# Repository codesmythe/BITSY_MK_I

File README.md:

This board is designed to run the [EmuTOS](https://emutos.sourceforge.io) operating system. EmuTOS is an open-source variant of the Atari ST TOS operating system.

BITSY Mark I is part of system containing this board, a [XOSERA_RCBUS](https://github.com/codesmythe/XOSERA_RCBUS) board for VGA output, a [KEMOJO](https://github.com/codesmythe/KEMOJO) board for
PS/2 keyboard and mouse input, and an RCBus backplane board such as an [SC147](https://smallcomputercentral.com/rcbus/sc100-series/sc147-modular-backplane-rc2014/). Together, this system can run full GUI EmuTOS with 640x240 graphics in 16 colors.

This SBC can also be used by itself, in EmuTOS command-line mode, using the on-board UART for serial input and output at 57600 baud.

But please do note that it is early days for this system, so there are undiscovered bugs looming. In particular, you may see occasional graphical artifacts in EmuTOS as the driver is debugged.

|                      |
| :----------------------------------------------------------: |
| Full BITSY system running [Teradesk](https://github.com/freemint/teradesk) with color icons on EmuTOS. Free memory shows 16 MB SRAM SIMM in use. |

## Table of Contents
* [Hardware Documentation](#hardware-documentation)
  * [Schematic](#schematic)
  * [Connectors](#connectors)
  * [Jumpers](#jumpers)
  * [SRAM Choice](#sram-choice)
  * [Bill of Materials](#bill-of-materials)
* [Firmware Documentation](#firmware-documentation)
   * [ROM: EmuTOS](#rom-emutos)
   * [SPLD Fuse Maps](#spld-fuse-maps)

## Hardware Documentation

### Schematics

This four layer, 102mm x 102mm board was created using [Kicad](https://www.kicad.org) version 8.0. The KiCad files are
available in this repository.

The image below shows the top level schematic page. Click on it to download the full eight page schematic in PDF format.

### Connectors

| Reference | Description                                                  |
| --------- | ------------------------------------------------------------ |
| J1        | Barrel jack connection for a 2A, 5V, 2mm power supply.       |
| J2        | Six pin male header for connection to a USB-to-serial adapters. Uses the [FTDI Friend](https://www.adafruit.com/product/284) pinout. |
| J3        | Five pin male header for connection to a DS3231 Real Time Clock module. |
| J5        | 40-pin connection to an RCBus 40-pin or 80-pin backplane.    |

### Jumpers

| Refence | Picture | Description                                                  | Comment                                                      |
| ------- | ------- | ------------------------------------------------------------ | ------------------------------------------------------------ |
| JP1     |         | Connects RCBus /INT (pin 22) to 68K interrupt level 4 (1-2) or level 2 (2-3) | When using BITSY Mark I with the [XOSERA_RCBUS](https://github.com/codesmythe/XOSERA_RCBUS) board, jumper pins 1-2 to use 68K /INT4. |
| JP2     |         | When closed, connects RCBus USER1/INT1 (pin 37) to MFP GPIO4. When open, RCBus pin 37 is unconnected. | Close this jumper when using the [KEMOJO](https://github.com/codesmythe/KEMOJO) board for PS/2 keyboard, PS/2 mouse and joystick support. |

### SRAM Choice

Memory for this board is hosted on a custom 72-pin "SRAM SIMM" board. Though SIMMs are conventionally associated with DRAMs, these custom modules present a static RAM (SRAM) interface to the motherboard. Thus they have a demultiplexed address bus and use SRAM control signals such as chip enable, output enable and write enables.

> [!WARNING]
> BITSY_MK_I is **completely incompatible** with conventional DRAM SIMMs.

#### 1 MB SRAM SIMM

The 1 MB through hole version is a good choice to start with, as it is inexpensive and easy to solder. Gerbers for the boards are available in this repository. So if you
are ordering a BITSY board from a PCB maker, also order one of these memory modules.

#### 16 MB SRAM SIMM

If you end up using the system regularly, I'd suggest upgrading to a 16 MB "SRAM SIMM" I have created. If interested, please contact me about purchasing a 16 MB module, which run about USD $36 each. Alternatively, you can have JLCPCB assemble them yourself using the design files in [this](http://github.com/codesmythe/SRAM_SIMM_16MB) repository.

### Bill of Materials

[Text file parts list](BITSY_V1E_mouser.txt) for pasting into the [Mouser BOM tool](https://www.mouser.com/Bom/CopyPaste) (login required).

To obtain a BITSY Mark I PCB, download these [Gerbers](https://github.com/codesmythe/BITSY_MK_I/raw/refs/heads/main/BITSY_Mark_I_V1E.zip) for use at your preferred PCB manufacturer. I use JLCPCB.

| Component Type     | Reference            | Qty  | Description                                                  | Part                                                         |
| ------------------ | -------------------- | ---- | ------------------------------------------------------------ | ------------------------------------------------------------ |
| CF Adapter         | none                 | 1    | Compact Flash Male IDE 44pin adapter                         | eBay or Amazon: search for "Compact Flash Male IDE 44pin adapter" |
| RTC                | none                 | 1    | (optional) DS3231 I2C Real Time Clock module                 | Amazon: search for "DS3231 rtc module". Get a black one with 5-pin female connector and yellow battery. |
| Capacitor          | C1-C4,C7-C12,C14,C15 | 12   | 0.1 uF, MLCC, 5 mm Pitch                                     | Mouser [594-K104K15X7RF5TH5](https://www.mouser.com/ProductDetail/594-K104K15X7RF5TH5) |
| Capacitor          | C92,C93              | 2    | Electrolytic Capacitor, Radial, 6.3V 470uF, 6.3D, 2.5P       | Mouser [80-ESK477M6R3AE3AA](https://www.mouser.com/ProductDetail/80-ESK477M6R3AE3AA) |
| Capacitor          | C94                  | 1    | MLCC, Leaded 100pF 50V 5% C0G 5mm                            | Mouser [594-K101J15C0GF5TH5](https://www.mouser.com/ProductDetail/594-K101J15C0GF5TH5) |
| Capacitor          | C97,C98              | 2    | Electrolytic Capacitor, Radial, 16V, 100uF, 5D, 2.5P         | Mouser [667-ECA-1CM101I](https://www.mouser.com/ProductDetail/667-ECA-1CM101I) |
| Capacitor          | CON1                 | 1    | Audio Jack, 3 Poles, Switched TR Poles                       | Mouser [490-SJ1-3535NG](https://www.mouser.com/ProductDetail/490-SJ1-3535NG) |
| Diode              | D1                   | 1    | Green LED, through hole, 5 mm pitch                          | Mouser [859-LTL-307GLC](https://www.mouser.com/ProductDetail/859-LTL-307GLC) |
| Jumper             | J1                   | 1    | DC Barrel Jack                                               | Mouser [490-PJ-002A](https://www.mouser.com/ProductDetail/490-PJ-002A) |
| Jumper             | J2                   | 1    | 1x6 right angle pin header                                   | Mouser [737-PH1RB-06-UA](https://www.mouser.com/ProductDetail/737-PH1RB-06-UA) |
| Jumper             | J3                   | 1    | 1x5 right angle pin header                                   | Mouser [737-PH1RB-05-UA](https://www.mouser.com/ProductDetail/737-PH1RB-05-UA) |
| Jumper             | J5                   | 1    | 1x40 right angle pin header                                  | Mouser [710-61304011021](https://www.mouser.com/ProductDetail/710-61304011021) |
| Jumper             | JP1                  | 1    | 1x3 straight pin header                                      | Mouser [200-TSW10307TS](https://www.mouser.com/ProductDetail/200-TSW10307TS) |
| Jumper             | JP2                  | 1    | 1x2 straight pin header                                      | Mouser [200-TSW10207TS](https://www.mouser.com/ProductDetail/200-TSW10207TS) |
| Transistor         | Q1                   | 1    | 2N7000  MOSFET in TO92                                       | Mouser [512-2N7000](https://www.mouser.com/ProductDetail/512-2N7000) |
| Resistor           | R2                   | 1    | 470 ohm, axial, 1% tolerance, 1/4 W                          | Mouser [603-MFR-25FTE52-470R](https://www.mouser.com/ProductDetail/603-MFR-25FTE52-470R) |
| Resistor           | R3                   | 1    | 10K ohm, axial, 1% tolerance, 1/4 W                          | Mouser [603-MFR-25FTE52-10K](https://www.mouser.com/ProductDetail/603-MFR-25FTE52-10K) |
| Resistor           | R84,R85              | 2    | 1K ohm, axial, 1% tolerance, 1/4 W                           | Mouser [603-MFR-25FTE52-1K](https://www.mouser.com/ProductDetail/603-MFR-25FTE52-1K) |
| Resistor           | R86,R87              | 2    | 1600 ohm, axial, 1% tolerance, 1/4 W                         | Mouser [603-MFR-25FTE52-1K6](https://www.mouser.com/ProductDetail/603-MFR-25FTE52-1K6) |
| Resistor           | R88-R90              | 3    | 3K ohm, axial, 1% tolerance, 1/4 W                           | Mouser [603-MFR-25FTE52-3K](https://www.mouser.com/ProductDetail/603-MFR-25FTE52-3K) |
| Resistor           | R97                  | 1    | 100 ohm, axial, 1% tolerance, 1/4 W                          | Mouser [603-MFR-25FBF52-100R](https://www.mouser.com/ProductDetail/603-MFR-25FBF52-100R) |
| Resistor           | RN1,RN2              | 2    | 4.7K ohm bussed network, 6 resistors, 7 pins, SIP            | Mouser [652-4607X-1LF-4.7K](https://www.mouser.com/ProductDetail/652-4607X-1LF-4.7K) |
| Switch             | SW1                  | 1    | Push button switch                                           | Mouser [179-TS026655BK160LCR](https://www.mouser.com/ProductDetail/179-TS026655BK160LCR) |
| Integrated Circuit | U1                   | 1    | MC68HC000 CPU in PLCC-68, 20 MHz                             | Ebay: search for "MC68HC000FN20"                             |
| Integrated Circuit | U2                   | 1    | TS68HC901 Multi Function Peripheral (MFP) chip in PLCC-52    | Ebay: search for "TS68HC901CFN8B"                            |
| Integrated Circuit | U3,U4                | 2    | 512k x 8 Flash ROM in PLCC-32                                | Mouser [579-39SF040554CNHET](https://www.mouser.com/ProductDetail/579-39SF040554CNHET) |
| Integrated Circuit | U7                   | 1    | MIC1232 CPU Supervisor in 8-pin DIP                          | Mouser [998-MIC1232NY](https://www.mouser.com/ProductDetail/998-MIC1232NY) |
| Integrated Circuit | U8-U11               | 4    | ATF22V10C-15PU, Simple PLD, 24 I/O in 24-pin DIP             | Mouser [556-AF22V10C15PU](https://www.mouser.com/ProductDetail/556-AF22V10C15PU) |
| Integrated Circuit | U12                  | 1    | AY-3-8913 Programmable Sound Generator (PSG) in 24-pin wide DIP | Ebay: search for "AY-3-8913"                                 |
| Integrated Circuit | U14,U15              | 2    | 74HCT245 Octal Bus Transceivers in 20-pin DIP                | Mouser [595-SN74HCT245N](https://www.mouser.com/ProductDetail/595-SN74HCT245N) |
| Oscillator         | X1                   | 1    | 16 MHz can oscillator in 8-pin DIP                           | Mouser [774-MXO45HST-3C-16.0](https://www.mouser.com/ProductDetail/774-MXO45HST-3C-16.0) |
| Oscillator         | X2                   | 1    | 7.3278 MHz can oscillator in 8-pin DIP                       | Mouser [774-MXO45HS-3C-7.3](https://www.mouser.com/ProductDetail/774-MXO45HS-3C-7.3) |
| Oscillator         | X3                   | 1    | 2 MHz can oscillator in 8-pin DIP                            | Mouser [774-MXO45HS2C2M0000](https://www.mouser.com/ProductDetail/774-MXO45HS2C2M0000) |
| Socket             | Socket for U1        | 1    | 68-pin PLCC socket                                           | Mouser [575-682444](https://www.mouser.com/ProductDetail/575-682444) |
| Socket             | Socket for U2        | 1    | 52-pin PLCC socket                                           | Mouser [575-945224](https://www.mouser.com/ProductDetail/575-945224) |
| Socket             | Socket for U3,U4     | 2    | 32-pin PLCC socket                                           | Mouser [649-54020-32030LF](https://www.mouser.com/ProductDetail/649-54020-32030LF) |
| Socket             | Socket U5            | 1    | SIMM Connectors 72 POS SIMM VERT TIN                         | Mouser [571-5822021-4](https://www.mouser.com/ProductDetail/571-5822021-4) |
| Socket             | Socket for U7        | 1    | 8-pin DIP socket                                             | Mouser [737-ICM-308-1-GT-HT](https://www.mouser.com/ProductDetail/737-ICM-308-1-GT-HT) |
| Socket             | Socket for U8-U11    | 4    | 24-pin DIP socket                                            | Mouser [737-ICM-324-1-GT-HT](https://www.mouser.com/ProductDetail/737-ICM-324-1-GT-HT) |
| Socket             | Socket for U12       | 1    | 24-pin wide DIP socket                                       | Mouser [737-ICM-624-1-GT-HT](https://www.mouser.com/ProductDetail/737-ICM-624-1-GT-HT) |
| Socket             | Socket for U14,U15   | 2    | 20-pin DIP socket                                            | Mouser [737-ICM-320-1-GT-HT](https://www.mouser.com/ProductDetail/737-ICM-320-1-GT-HT) |
| Socket             | Socket for X1-X3     | 3    | 8-pin oscillator socket                                      | Mouser [535-1108800](https://www.mouser.com/ProductDetail/535-1108800) |

## Firmware Documentation

### ROM: EmuTOS

As mentioned, this board is designed to run EmuTOS. The source code for my fork of EmuTOS to support various 68K single
board computers, including this one, can be found [here](https://github.com/codesmythe/emutos). The version of EmuTOS in the fork is
based on EmuTOS version 1.4.

Two default configurations are provided by the ROM binaries in this repository. Other configurations are
available by compiling EmuTOS from the source code linked above.

#### Configuration: Using serial port command line I/O interface

The first configuraiton uses the UART provided by the MC68901 and runs EmuTOS in "serial console" mode. 
In this configuration, 1 MB of SRAM is supported, which can be provided using two standard 512K 32-pin DIP SRAMs 
like the AS6C4008 mounted on an "SRAM SIMIM" adapter mentioned above. The "EmuCON" part of EmuTOS provides a command line interface. Here are the even and odd ROM binaries for this configuration:

| ROM  | Size   | File | 
| ---- | ------ | ---- |
| Even | 512KB  | [bitsy_v1_sercon_1mb_20251123.even.bin](https://github.com/codesmythe/BITSY_MK_I/raw/refs/heads/main/ROMS/bitsy_v1_sercon_1mb_20251123.even.bin) | 
| Odd  | 512KB  | [bitsy_v1_sercon_1mb_20251123.odd.bin](https://github.com/codesmythe/BITSY_MK_I/raw/refs/heads/main/ROMS/bitsy_v1_sercon_1mb_20251123.odd.bin) | 

#### Configuration: Using VGA and PS/2 support to run EmuTOS GUI (GEM)

The second configuration runs EmuTOS in full GUI (GEM) mode and requires the use of the 
[XOSERA_RCBUS](https://github.com/codesmythe/XOSERA_RCBUS) and [KEMOJO](https://github.com/codesmythe/KEMOJO) boards to provide VGA output and PS/2 keyboard and mouse input. In this configuration, at least 4MB is suggested so I recommend using the 16 MB "SRAM SIMM" module described above. It is possible to run GEM mode in 1 MB of RAM, but for you now you will have configure EmuTOS and compile it from source. Here are the even and odd ROM binaries for the 14 MB configuration:

| ROM  | Size   | File | 
| ---- | ------ | ---- |
| Even | 512KB  | [bitsy_v1_gem_14mb_20251123.even.bin](https://github.com/codesmythe/BITSY_MK_I/raw/refs/heads/main/ROMS/bitsy_v1_gem_14mb_20251123.even.bin) |
| Odd  | 512KB  | [bitsy_v1_gem_14mb_20251123.odd.bin](https://github.com/codesmythe/BITSY_MK_I/raw/refs/heads/main/ROMS/bitsy_v1_gem_14mb_20251123.odd.bin)   |

#### Memory Map

| Address Range | Use  |
| --------------------------------|-----------------------------------------------------------------------------|
| 00_0000 to (0F_FFFF or DF_FFFF) | 1 MB or 14 MB RAM                                                           |
| E0_0000 to EF_FFFF              | 1 MB ROM                                                                    |
| F0_0000 to F0_003F              | IDE (mirrored every 64 bytes in the 4K byte range from F0_0000 to F0_0FFF.) |
| FF_0000 to FF_FFFF              | 64K RC2014 IO (IOREQ). Includes the on-board PSG and MFP.                   |

#### I/O Map

These addresses (and the IDE addresses above) are the same as the Atari ST for software compatibility.

| Address Range      | Use                                                                                               | 
|--------------------|---------------------------------------------------------------------------------------------------|
| FF_FA01 to FF_FA2F | MFP (odd byte lane) mirrored every 48 bytes in the 256 byte range from FF_FA00 to FA_FAFF.)       |
| FF_8800 to FF_8803 | PSG (even byte lane) mirrored every  4 bytes in the 256 byte range from FF_8800 to FF_88FF.)      | 
| FF_0191 to FF_01A1 | TL16C550 UART on KEMOJO board (odd byte lane), if using default setting of 0xC8 on that board.    |
| FF_81c1 to FF_81E1 | Xosera registers, if using default setting of 0xE0 on that board.                                 |

### SPLD Fuse Maps

BITSY Mark I uses four ATF22V10/GAL22V10 SPLDs (U8 - U11) for address decode and various other control logic. The SPLD fuse maps (JED files) can be downloaded via the links in the table below. The SPLDs are implemented using Flash/EEPROM technology and can be programmed by commonly available EPROM programmers, such as MiniPro TL866 II+ or newer. The source code (PLD) files  are also provided in the repository. If needed, they can be modified. Use [GALasm](https://github.com/daveho/GALasm)  to compile PLD files to JED fuse maps.

Note that there are separate fuse files for U9/HIDECODE depending on whether you are using 1 MB or 14 MB SRAM.

| Reference  | Source File                            | JED File                                                     | Functions                                      |
| ---------- | -------------------------------------- | ------------------------------------------------------------ | ---------------------------------------------- |
| U8         | [MEMCTL.PLD](MEMCTL.PLD)               | [MEMCTL.jed](https://github.com/codesmythe/BITSY_MK_I/raw/refs/heads/main/MEMCTL.jed) | Interrupt control, RCBus interface             |
| U9 (1 MB)  | [HIDECODE.PLD](HIDECODE.PLD)           | [HIDECODE.jed](https://github.com/codesmythe/BITSY_MK_I/raw/refs/heads/main/HIDECODE.jed) | Decode high part of address bus for 1 MB SRAM  |
| U9 (16 MB) | [HIDECODE_16MB.PLD](HIDECODE_16MB.PLD) | [HIDECODE_16MB.jed](https://github.com/codesmythe/BITSY_MK_I/raw/refs/heads/main/HIDECODE_16MB.jed) | Decode high part of address bus for 14 MB SRAM |
| U10        | [CONTROL.PLD](CONTROL.PLD)             | [CONTROL.jed](https://github.com/codesmythe/BITSY_MK_I/raw/refs/heads/main/CONTROL.jed) | Wait states, DTACK generation, IDE interface   |
| U11        | [DECODE.PLD](DECODE.PLD)               | [DECODE.jed](https://github.com/codesmythe/BITSY_MK_I/raw/refs/heads/main/DECODE.jed) | Decode low part of address bus                 |

### Acknowledgements

When I designed this board, I took ideas and inspiration from these projects:

- Bill Shen's [Tiny68K](https://www.retrobrewcomputers.org/doku.php?id=boards:sbc:tiny68k) board.

- John Coffmans's [Mini-68K](https://www.retrobrewcomputers.org/doku.php?id=boards:ecb:mini-68k:start) ECB board.

- Clements, Alan. [*Microprocessor Systems Design: 68000 Hardware, Software and Interfacing, Third Edition*](https://archive.org/details/microprocessor-systems-design-alan-clements-9780534948221)
 PWS Publishing Company, 1997.

- [Atari ST schematics](https://archive.org/details/Atari_520ST_Schematic_1985/mode/1up)

- Various [Motorola Application Notes](http://www.bitsavers.org/components/motorola/_appNotes/) from back in the day.

The sound output circuit is borrowed from https://hw.speccy.cz/melodik2.html by way of https://github.com/electrified/rc2014-ym2149/blob/main/README.md

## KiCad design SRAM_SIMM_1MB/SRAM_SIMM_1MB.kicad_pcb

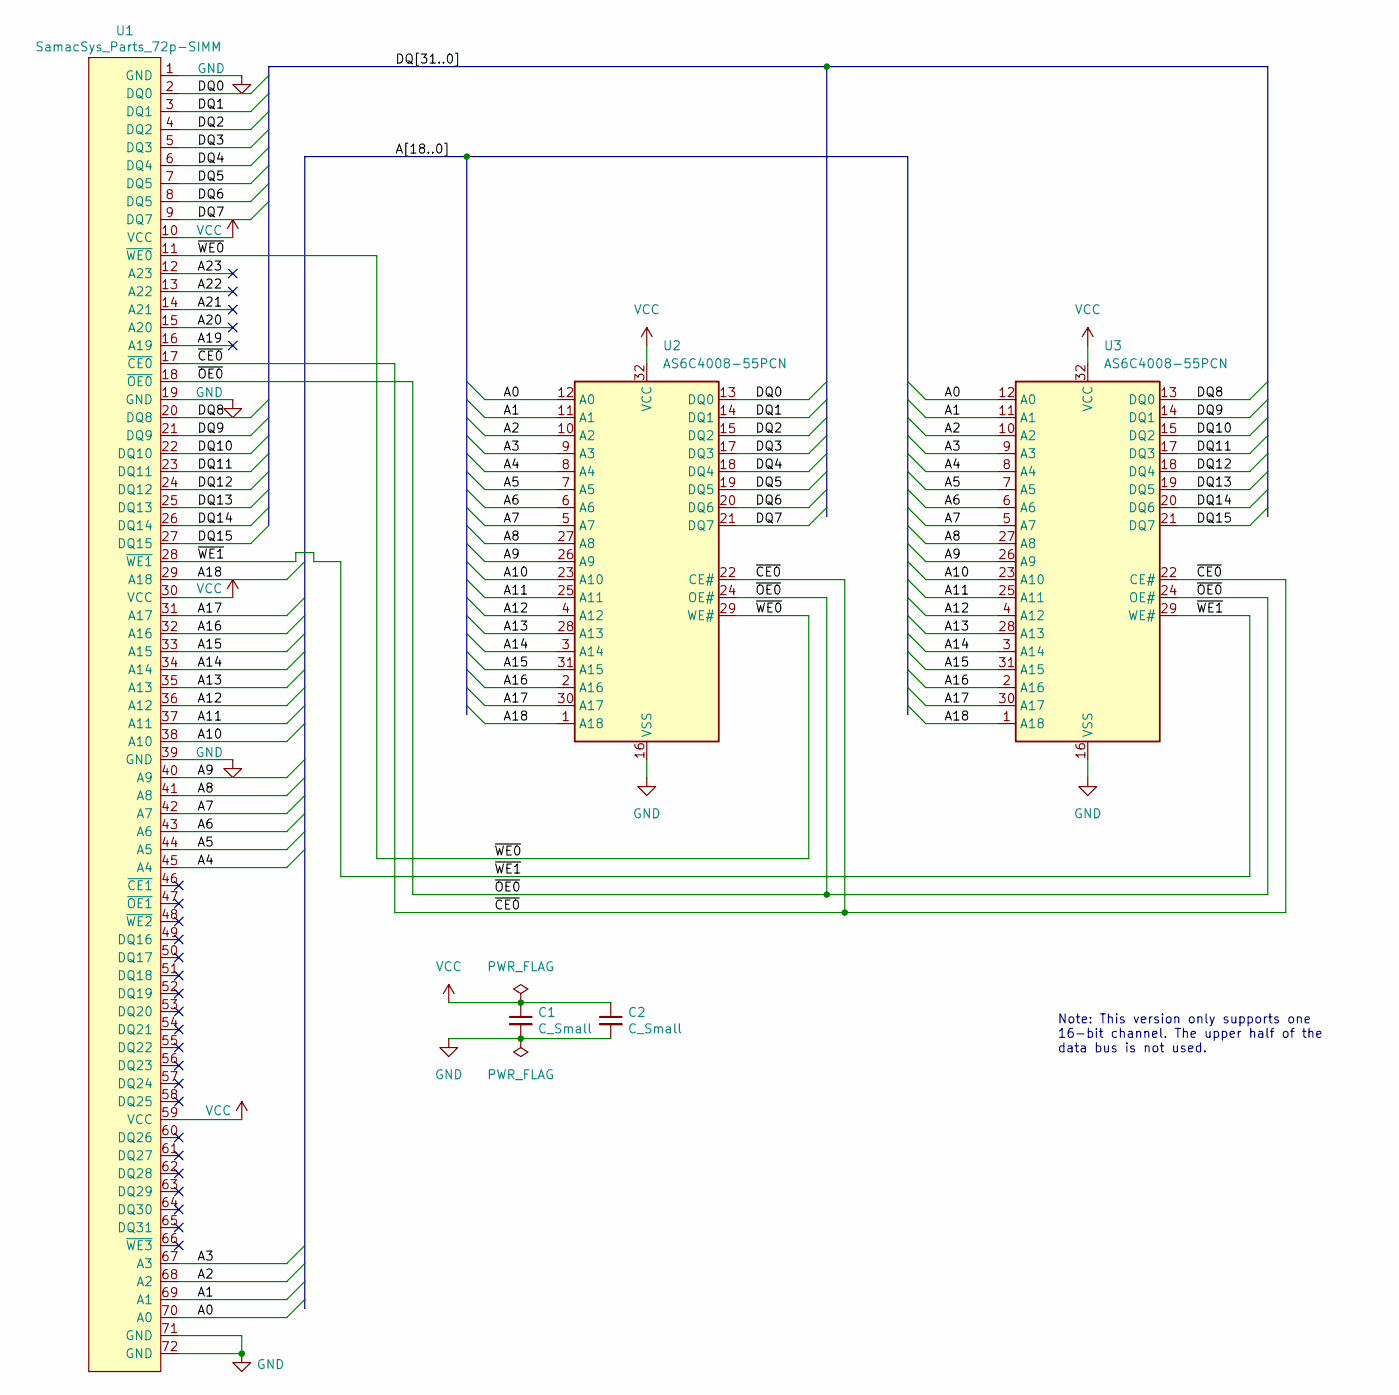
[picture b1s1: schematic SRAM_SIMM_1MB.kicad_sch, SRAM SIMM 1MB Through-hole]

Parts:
C1, C2: C_Small; C_Rect_L7.0mm_W2.5mm_P5.00mm; MouserPN 594-K104K15X7RF5TH5; LCSC C2167231
U1: SamacSys_Parts_72p-SIMM; 72p-SIMM; MouserPN 571-5822021-4; DigiKeyPN A114049-ND
U2, U3: AS6C4008-55PCN; DIP-32_W15.24mm_Socket_LongPads; MouserPN 913-AS6C4008-55PCN; LCSC C1350141

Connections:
/A0: U1.70 (A0), U2.12 (A0), U3.12 (A0)
/A1: U1.69 (A1), U2.11 (A1), U3.11 (A1)
/A2: U1.68 (A2), U2.10 (A2), U3.10 (A2)
/A3: U1.67 (A3), U2.9 (A3), U3.9 (A3)
/A4: U1.45 (A4), U2.8 (A4), U3.8 (A4)
/A5: U1.44 (A5), U2.7 (A5), U3.7 (A5)
/A6: U1.43 (A6), U2.6 (A6), U3.6 (A6)
/A7: U1.42 (A7), U2.5 (A7), U3.5 (A7)
/A8: U1.41 (A8), U2.27 (A8), U3.27 (A8)
/A9: U1.40 (A9), U2.26 (A9), U3.26 (A9)
/A10: U1.38 (A10), U2.23 (A10), U3.23 (A10)
/A11: U1.37 (A11), U2.25 (A11), U3.25 (A11)
/A12: U1.36 (A12), U2.4 (A12), U3.4 (A12)
/A13: U1.35 (A13), U2.28 (A13), U3.28 (A13)
/A14: U1.34 (A14), U2.3 (A14), U3.3 (A14)
/A15: U1.33 (A15), U2.31 (A15), U3.31 (A15)
/A16: U1.32 (A16), U2.2 (A16), U3.2 (A16)
/A17: U1.31 (A17), U2.30 (A17), U3.30 (A17)
/A18: U1.29 (A18), U2.1 (A18), U3.1 (A18)
/A19: U1.16 (A19)
/A19_1: U1.16 (A19)
/A20: U1.15 (A20)
/A20_1: U1.15 (A20)
/A21: U1.14 (A21)
/A21_1: U1.14 (A21)
/A22: U1.13 (A22)
/A22_1: U1.13 (A22)
/A23: U1.12 (A23)
/A23_1: U1.12 (A23)
/DQ0: U1.2 (DQ0), U2.13 (DQ0)
/DQ1: U1.3 (DQ1), U2.14 (DQ1)
/DQ2: U1.4 (DQ2), U2.15 (DQ2)
/DQ3: U1.5 (DQ3), U2.17 (DQ3)
/DQ4: U1.6 (DQ4), U2.18 (DQ4)
/DQ5: U1.7 (DQ5), U2.19 (DQ5)
/DQ6: U1.8 (DQ5), U2.20 (DQ6)
/DQ7: U1.9 (DQ7), U2.21 (DQ7)
/DQ8: U1.20 (DQ8), U3.13 (DQ0)
/DQ9: U1.21 (DQ9), U3.14 (DQ1)
/DQ10: U1.22 (DQ10), U3.15 (DQ2)
/DQ11: U1.23 (DQ11), U3.17 (DQ3)
/DQ12: U1.24 (DQ12), U3.18 (DQ4)
/DQ13: U1.25 (DQ13), U3.19 (DQ5)
/DQ14: U1.26 (DQ14), U3.20 (DQ6)
/DQ15: U1.27 (DQ15), U3.21 (DQ7)
/~CE0: U1.17 (~CE0), U2.22 (CE#), U3.22 (CE#)
/~OE0: U1.18 (~OE0), U2.24 (OE#), U3.24 (OE#)
/~WE0: U1.11 (~WE0), U2.29 (WE#)
/~WE1: U1.28 (~WE1), U3.29 (WE#)
GND: C1.2, C2.2, U1.1 (GND), U1.19 (GND), U1.39 (GND), U1.71 (GND), U1.72 (GND), U2.16 (VSS), U3.16 (VSS)
VCC: C1.1, C2.1, U1.10 (VCC), U1.30 (VCC), U1.59 (VCC), U2.32 (VCC), U3.32 (VCC)

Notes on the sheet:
Note: This version only supports one 16-bit channel. The upper half of the data bus is not used.

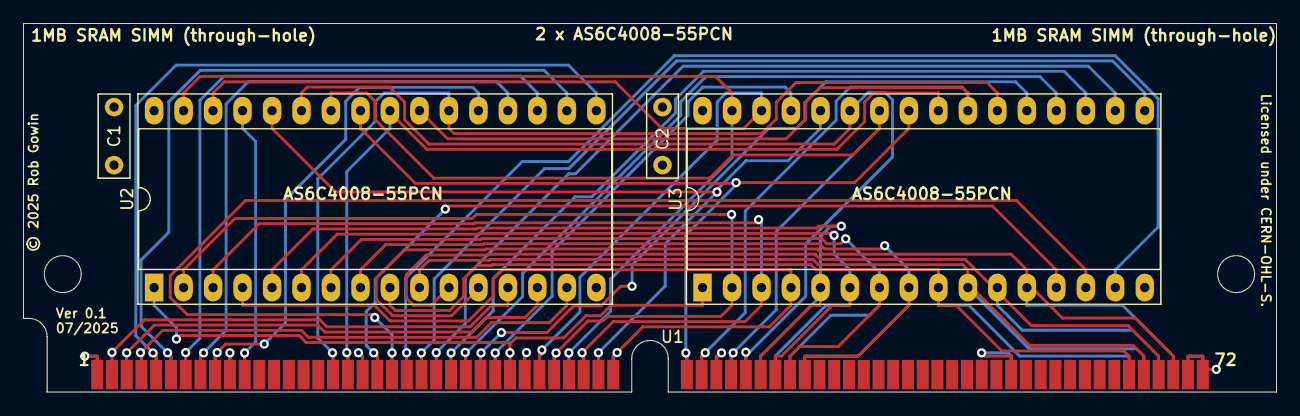
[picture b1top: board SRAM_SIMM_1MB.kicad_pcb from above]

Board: 4 copper layers, 107.9 x 31.8 mm, 5 parts (0 on the bottom side), 41 nets.

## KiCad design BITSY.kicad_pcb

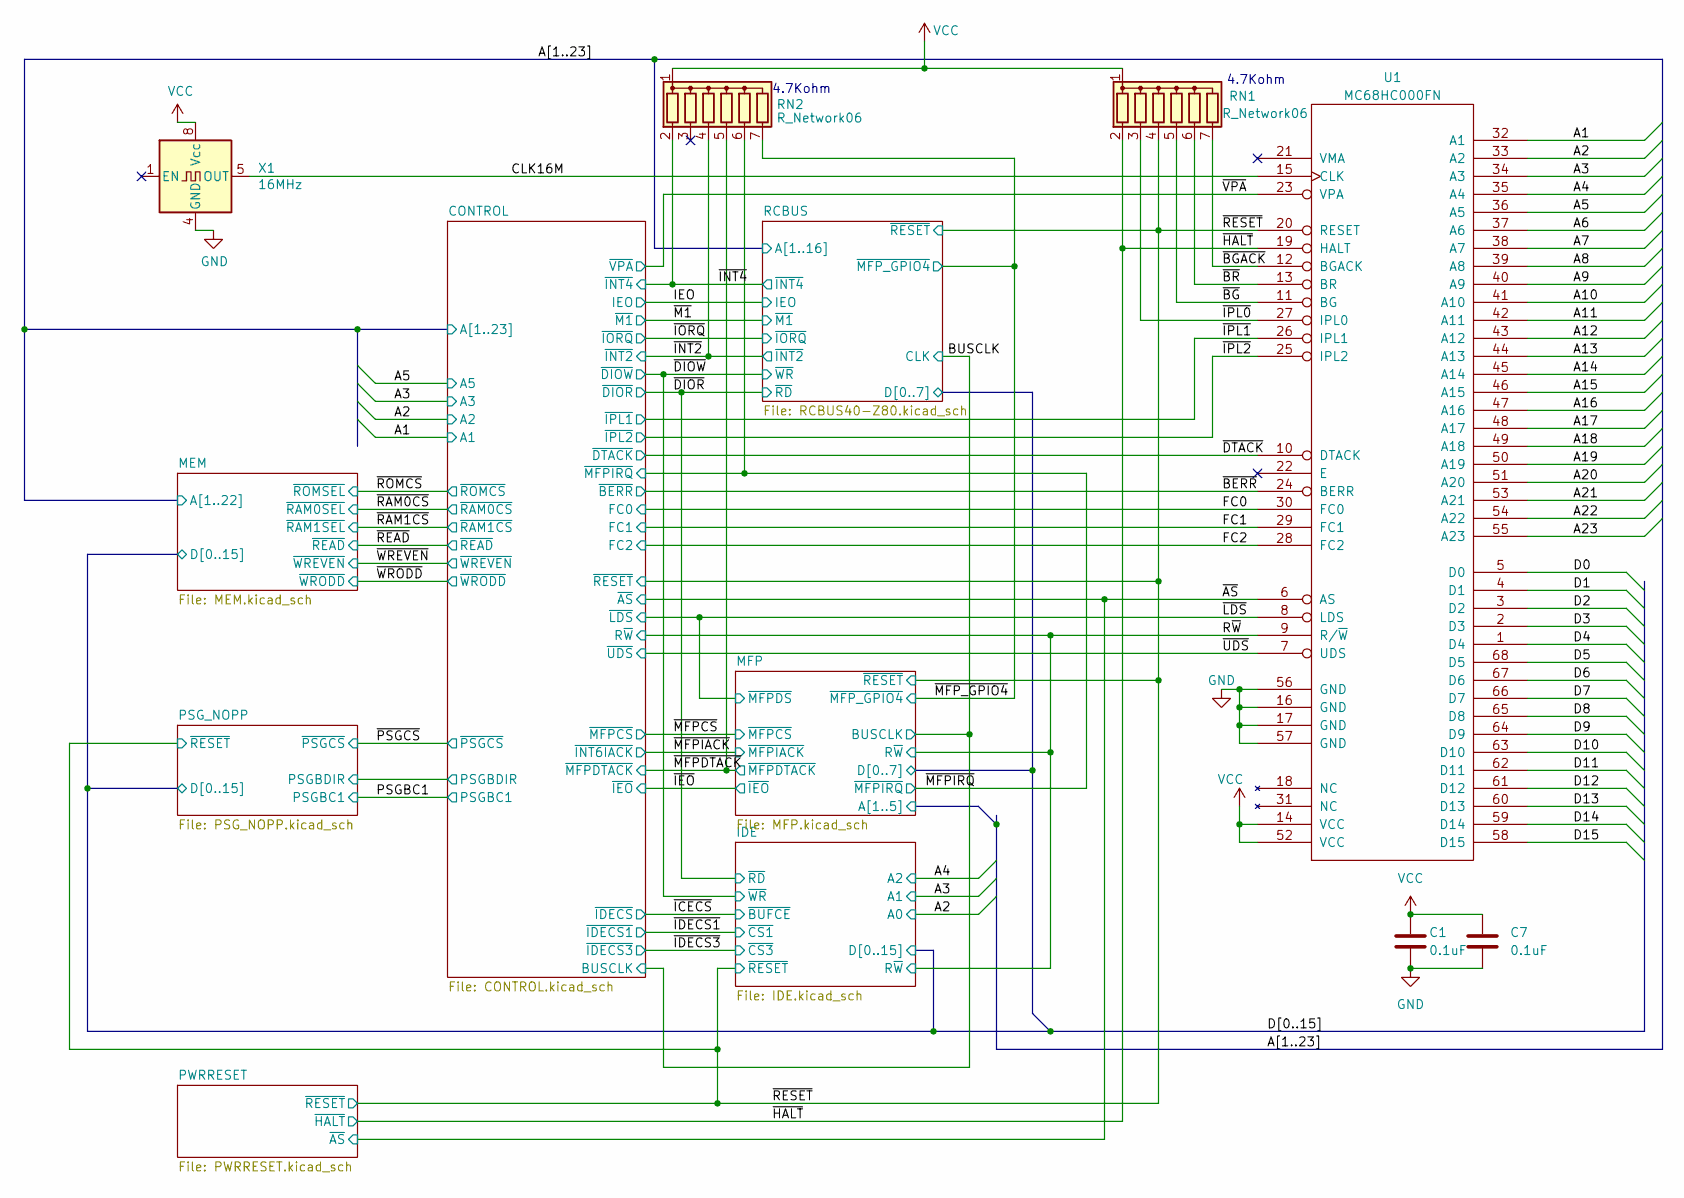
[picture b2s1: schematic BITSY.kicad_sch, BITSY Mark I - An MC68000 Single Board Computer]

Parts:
C1, C7: 0.1uF; C_Rect_L7.0mm_W2.0mm_P5.00mm; PartNum00 594-K104K15X7RF5TH5
RN1, RN2: R_Network06; R_Array_SIP7; PartNum00 652-4607X-1LF-4.7K
U1: MC68HC000FN; PLCC-68_THT-Socket; PartNum00 MC68HC000FN20
X1: 16MHz; Oscillator_DIP-8; PartNum00 774-MXO45HST-3C-16.0

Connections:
/A1: U1.32 (A1); also elsewhere on the board
/A2: U1.33 (A2); also elsewhere on the board
/A3: U1.34 (A3); also elsewhere on the board
/A4: U1.35 (A4); also elsewhere on the board
/A5: U1.36 (A5); also elsewhere on the board
/A6: U1.37 (A6); also elsewhere on the board
/A7: U1.38 (A7); also elsewhere on the board
/A8: U1.39 (A8); also elsewhere on the board
/A9: U1.40 (A9); also elsewhere on the board
/A10: U1.41 (A10); also elsewhere on the board
/A11: U1.42 (A11); also elsewhere on the board
/A12: U1.43 (A12); also elsewhere on the board
/A13: U1.44 (A13); also elsewhere on the board
/A14: U1.45 (A14); also elsewhere on the board
/A15: U1.46 (A15); also elsewhere on the board
/A16: U1.47 (A16); also elsewhere on the board
/A17: U1.48 (A17); also elsewhere on the board
/A18: U1.49 (A18); also elsewhere on the board
/A19: U1.50 (A19); also elsewhere on the board
/A20: U1.51 (A20); also elsewhere on the board
/A21: U1.53 (A21); also elsewhere on the board
/A22: U1.54 (A22); also elsewhere on the board
/A23: U1.55 (A23); also elsewhere on the board
/CLK16M: U1.15 (CLK), X1.5 (OUT)
/D0: U1.5 (D0); also elsewhere on the board
/D1: U1.4 (D1); also elsewhere on the board
/D2: U1.3 (D2); also elsewhere on the board
/D3: U1.2 (D3); also elsewhere on the board
/D4: U1.1 (D4); also elsewhere on the board
/D5: U1.68 (D5); also elsewhere on the board
/D6: U1.67 (D6); also elsewhere on the board
/D7: U1.66 (D7); also elsewhere on the board
/D8: U1.65 (D8); also elsewhere on the board
/D9: U1.64 (D9); also elsewhere on the board
/D10: U1.63 (D10); also elsewhere on the board
/D11: U1.62 (D11); also elsewhere on the board
/D12: U1.61 (D12); also elsewhere on the board
/D13: U1.60 (D13); also elsewhere on the board
/D14: U1.59 (D14); also elsewhere on the board
/D15: U1.58 (D15); also elsewhere on the board
/FC0: U1.30 (FC0); also elsewhere on the board
/FC1: U1.29 (FC1); also elsewhere on the board
/FC2: U1.28 (FC2); also elsewhere on the board
/R~W: U1.9 (R/~W); also elsewhere on the board
/~AS: U1.6 (AS); also elsewhere on the board
/~BERR: U1.24 (BERR); also elsewhere on the board
/~BGACK: RN1.7 (R6), U1.12 (BGACK)
/~BG: RN1.5 (R4), U1.11 (BG)
/~BR: RN1.6 (R5), U1.13 (BR)
/~DTACK: U1.10 (DTACK); also elsewhere on the board
/~HALT: RN1.2 (R1), U1.19 (HALT); also elsewhere on the board
/~INT2: RN2.4 (R3); also elsewhere on the board
/~INT4: RN2.2 (R1); also elsewhere on the board
/~IPL0: RN1.3 (R2), U1.27 (IPL0)
/~IPL1: U1.26 (IPL1); also elsewhere on the board
/~IPL2: U1.25 (IPL2); also elsewhere on the board
/~LDS: U1.8 (LDS); also elsewhere on the board
/~MFPDTACK: RN2.5 (R4); also elsewhere on the board
/~MFPIRQ: RN2.6 (R5); also elsewhere on the board
/~MFP_GPIO4: RN2.7 (R6); also elsewhere on the board
/~RESET: RN1.4 (R3), U1.20 (RESET); also elsewhere on the board
/~UDS: U1.7 (UDS); also elsewhere on the board
/~VPA: U1.23 (VPA); also elsewhere on the board
GND: C1.2, C7.2, U1.16 (GND), U1.17 (GND), U1.56 (GND), U1.57 (GND), X1.4 (GND); also elsewhere on the board
VCC: C1.1, C7.1, RN1.1 (common), RN2.1 (common), U1.14 (VCC), U1.52 (VCC), X1.8 (Vcc); also elsewhere on the board

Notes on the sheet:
4.7Kohm

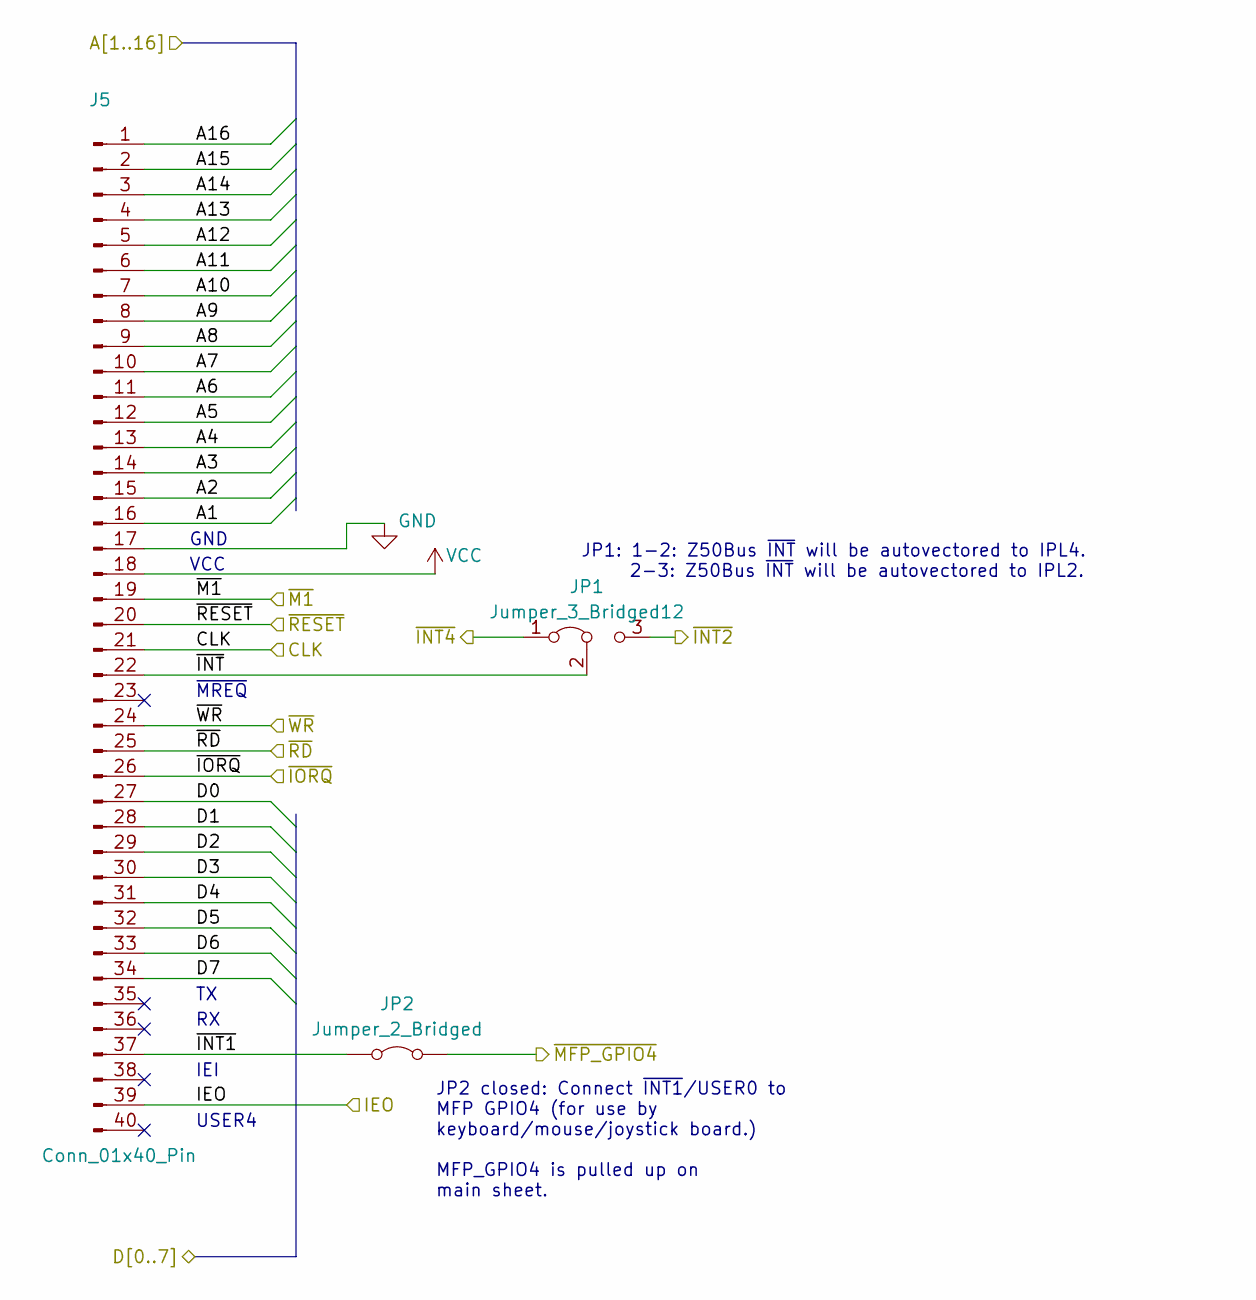
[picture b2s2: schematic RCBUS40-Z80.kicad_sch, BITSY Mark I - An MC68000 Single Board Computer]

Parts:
J5: Conn_01x40_Pin; PinHeader_1x40_P2.54mm_Vertical; PartNum00 710-61304011021
JP1: Jumper_3_Bridged12; PinHeader_1x03_P2.54mm_Vertical; PartNum00 200-TSW10307TS
JP2: Jumper_2_Bridged; PinHeader_1x02_P2.54mm_Vertical; PartNum00 200-TSW10207TS

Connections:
/A1: J5.16; also elsewhere on the board
/A2: J5.15; also elsewhere on the board
/A3: J5.14; also elsewhere on the board
/A4: J5.13; also elsewhere on the board
/A5: J5.12; also elsewhere on the board
/A6: J5.11; also elsewhere on the board
/A7: J5.10; also elsewhere on the board
/A8: J5.9; also elsewhere on the board
/A9: J5.8; also elsewhere on the board
/A10: J5.7; also elsewhere on the board
/A11: J5.6; also elsewhere on the board
/A12: J5.5; also elsewhere on the board
/A13: J5.4; also elsewhere on the board
/A14: J5.3; also elsewhere on the board
/A15: J5.2; also elsewhere on the board
/A16: J5.1; also elsewhere on the board
/BUSCLK: J5.21; also elsewhere on the board
/D0: J5.27; also elsewhere on the board
/D1: J5.28; also elsewhere on the board
/D2: J5.29; also elsewhere on the board
/D3: J5.30; also elsewhere on the board
/D4: J5.31; also elsewhere on the board
/D5: J5.32; also elsewhere on the board
/D6: J5.33; also elsewhere on the board
/D7: J5.34; also elsewhere on the board
/IEO: J5.39; also elsewhere on the board
/RCBUS/~INT1: J5.37, JP2.1 (A)
/RCBUS/~INT: J5.22, JP1.2 (C)
/~DIOR: J5.25; also elsewhere on the board
/~DIOW: J5.24; also elsewhere on the board
/~INT2: JP1.3 (B); also elsewhere on the board
/~INT4: JP1.1 (A); also elsewhere on the board
/~IORQ: J5.26; also elsewhere on the board
/~M1: J5.19; also elsewhere on the board
/~MFP_GPIO4: JP2.2 (B); also elsewhere on the board
/~RESET: J5.20; also elsewhere on the board
GND: J5.17; also elsewhere on the board
VCC: J5.18; also elsewhere on the board

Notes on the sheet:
VCC
JP2 closed: Connect ~{INT1}/USER0 to MFP GPIO4 (for use by keyboard/mouse/joystick board.) MFP_GPIO4 is pulled up on main sheet.
~{MREQ}
IEI
JP1: 1-2: Z50Bus ~{INT} will be autovectored to IPL4. 2-3: Z50Bus ~{INT} will be autovectored to IPL2.
GND
USER4

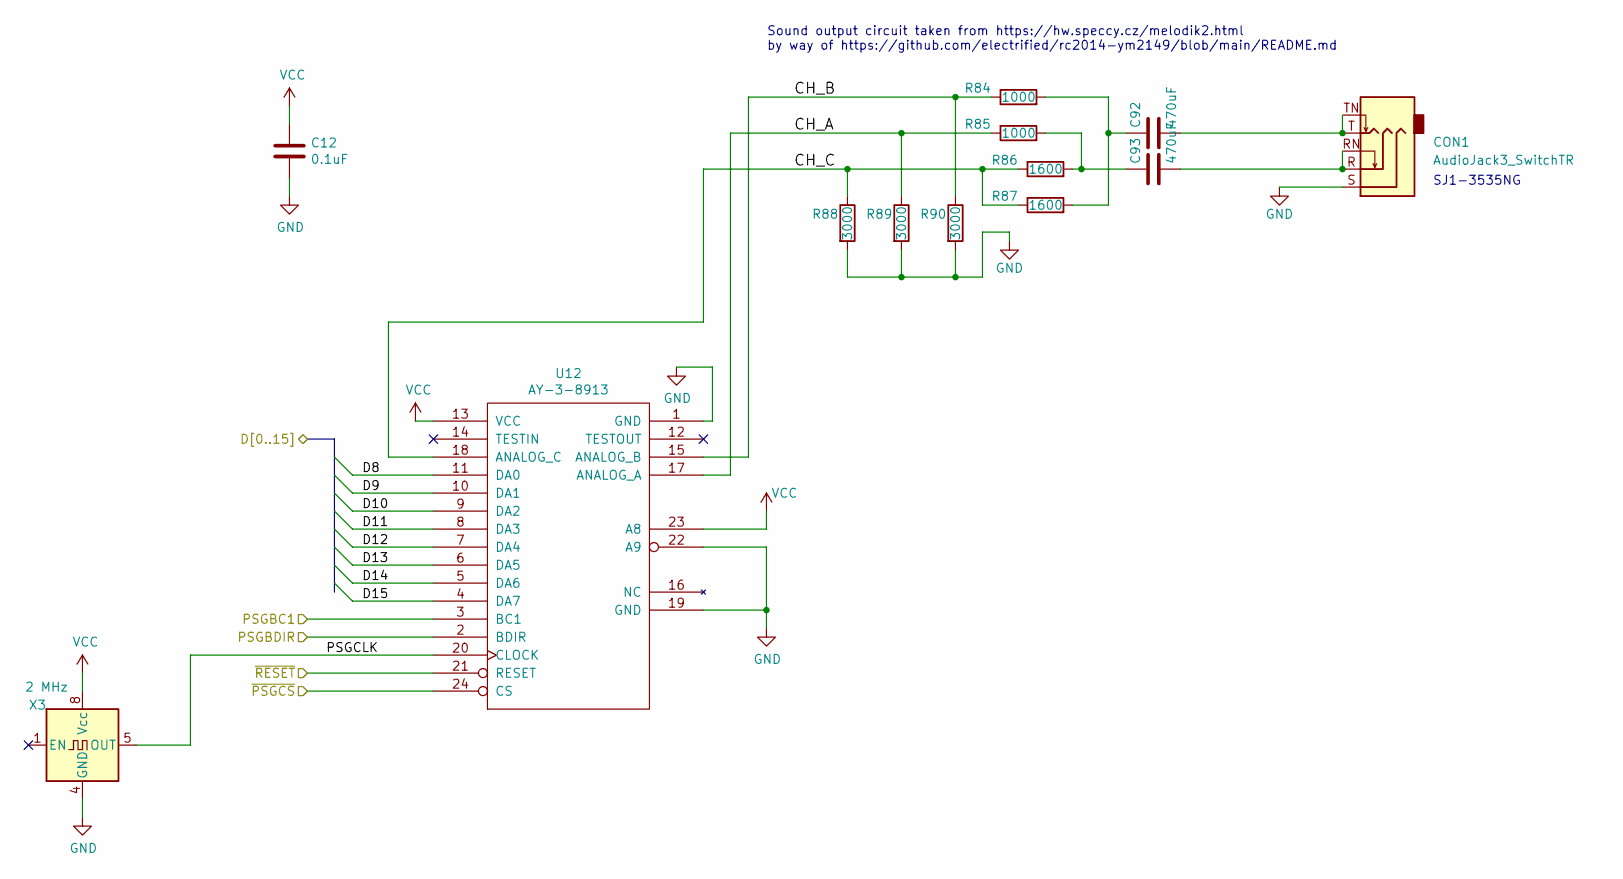
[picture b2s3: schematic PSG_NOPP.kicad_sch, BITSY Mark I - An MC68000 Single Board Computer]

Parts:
C12: 0.1uF; C_Rect_L7.0mm_W2.0mm_P5.00mm; PartNum00 594-K104K15X7RF5TH5
C92, C93: 470uF; CP_Radial_D6.3mm_P2.50mm; PartNum00 80-ESK477M6R3AE3AA
CON1: AudioJack3_SwitchTR; Jack_3.5mm_CUI_SJ1-3535NG_Horizontal; PartNum00 490-SJ1-3535NG
R84, R85: 1000; R_Axial_DIN0207_L6.3mm_D2.5mm_P7.62mm_Horizontal; PartNum00 603-MFR-25FTE52-1K
R86, R87: 1600; R_Axial_DIN0207_L6.3mm_D2.5mm_P7.62mm_Horizontal; PartNum00 603-MFR-25FTE52-1K6
R88, R89, R90: 3000; R_Axial_DIN0207_L6.3mm_D2.5mm_P7.62mm_Horizontal; PartNum00 603-MFR-25FTE52-3K
U12: AY-3-8913; DIP-24_W15.24mm_Socket_LongPads; PartNum00 AY-3-8913
X3: 2 MHz; Oscillator_DIP-8; PartNum00 774-MXO45HS2C2M0000

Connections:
/CONTROL/PSGBDIR: U12.2 (BDIR); also elsewhere on the board
/D8: U12.11 (DA0); also elsewhere on the board
/D9: U12.10 (DA1); also elsewhere on the board
/D10: U12.9 (DA2); also elsewhere on the board
/D11: U12.8 (DA3); also elsewhere on the board
/D12: U12.7 (DA4); also elsewhere on the board
/D13: U12.6 (DA5); also elsewhere on the board
/D14: U12.5 (DA6); also elsewhere on the board
/D15: U12.4 (DA7); also elsewhere on the board
/PSGBC1: U12.3 (BC1); also elsewhere on the board
/PSG_NOPP/CH_A: R85.1, R89.1, U12.17 (ANALOG_A)
/PSG_NOPP/CH_B: R84.1, R90.1, U12.15 (ANALOG_B)
/PSG_NOPP/CH_C: R86.1, R87.1, R88.1, U12.18 (ANALOG_C)
/PSG_NOPP/PSGCLK: U12.20 (CLOCK), X3.5 (OUT)
/~PSGCS: U12.24 (CS); also elsewhere on the board
/~RESET: U12.21 (RESET); also elsewhere on the board
GND: C12.2, CON1.S, R88.2, R89.2, R90.2, U12.1 (GND), U12.19 (GND), U12.22 (A9), X3.4 (GND); also elsewhere on the board
unnamed: C92.1, R84.2, R87.2
unnamed: C92.2, CON1.T, CON1.TN
unnamed: C93.1, R85.2, R86.2
unnamed: C93.2, CON1.R, CON1.RN
VCC: C12.1, U12.13 (VCC), U12.23 (A8), X3.8 (Vcc); also elsewhere on the board

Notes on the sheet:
SJ1-3535NG
Sound output circuit taken from https://hw.speccy.cz/melodik2.html by way of https://github.com/electrified/rc2014-ym2149/blob/main/README.md

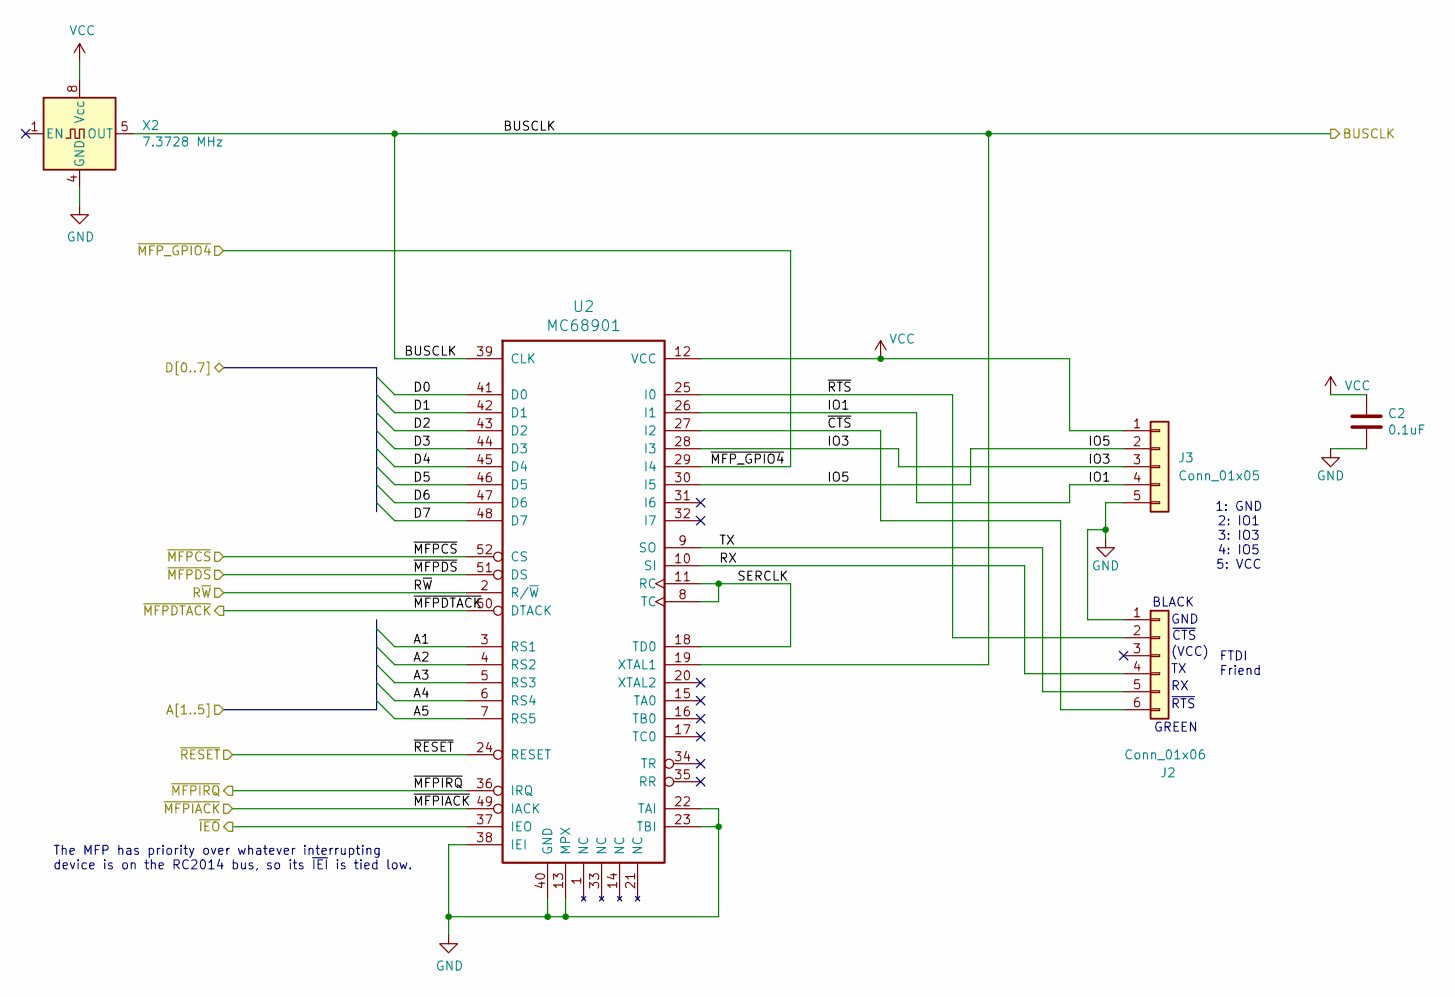
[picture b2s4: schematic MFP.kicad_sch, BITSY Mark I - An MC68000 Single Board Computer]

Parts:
C2: 0.1uF; C_Rect_L7.0mm_W2.0mm_P5.00mm; PartNum00 594-K104K15X7RF5TH5
J2: Conn_01x06; PinHeader_1x06_P2.54mm_Horizontal; PartNum00 737-PH1RB-06-UA
J3: Conn_01x05; PinHeader_1x05_P2.54mm_Horizontal; PartNum00 737-PH1RB-05-UA
U2: MC68901; PLCC-52_THT-Socket; PartNum00 TS68HC901CFN8B
X2: 7.3728 MHz; Oscillator_DIP-8; PartNum00 774-MXO45HS-3C-7.3

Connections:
/A1: U2.3 (RS1); also elsewhere on the board
/A2: U2.4 (RS2); also elsewhere on the board
/A3: U2.5 (RS3); also elsewhere on the board
/A4: U2.6 (RS4); also elsewhere on the board
/A5: U2.7 (RS5); also elsewhere on the board
/BUSCLK: U2.19 (XTAL1), U2.39 (CLK), X2.5 (OUT); also elsewhere on the board
/D0: U2.41 (D0); also elsewhere on the board
/D1: U2.42 (D1); also elsewhere on the board
/D2: U2.43 (D2); also elsewhere on the board
/D3: U2.44 (D3); also elsewhere on the board
/D4: U2.45 (D4); also elsewhere on the board
/D5: U2.46 (D5); also elsewhere on the board
/D6: U2.47 (D6); also elsewhere on the board
/D7: U2.48 (D7); also elsewhere on the board
/MFP/IO1: J3.4, U2.26 (I1)
/MFP/IO3: J3.3, U2.28 (I3)
/MFP/IO5: J3.2, U2.30 (I5)
/MFP/RX: J2.4, U2.10 (SI)
/MFP/SERCLK: U2.8 (TC), U2.11 (RC), U2.18 (TD0)
/MFP/TX: J2.5, U2.9 (SO)
/MFP/~CTS: J2.6, U2.27 (I2)
/MFP/~RTS: J2.2, U2.25 (I0)
/R~W: U2.2 (R/~W); also elsewhere on the board
/~IEO: U2.37 (IEO); also elsewhere on the board
/~LDS: U2.51 (DS); also elsewhere on the board
/~MFPCS: U2.52 (CS); also elsewhere on the board
/~MFPDTACK: U2.50 (DTACK); also elsewhere on the board
/~MFPIACK: U2.49 (IACK); also elsewhere on the board
/~MFPIRQ: U2.36 (IRQ); also elsewhere on the board
/~MFP_GPIO4: U2.29 (I4); also elsewhere on the board
/~RESET: U2.24 (RESET); also elsewhere on the board
GND: C2.2, J2.1, J3.5, U2.13 (MPX), U2.22 (TAI), U2.23 (TBI), U2.38 (IEI), U2.40 (GND), X2.4 (GND); also elsewhere on the board
VCC: C2.1, J3.1, U2.12 (VCC), X2.8 (Vcc); also elsewhere on the board

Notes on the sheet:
(VCC)
FTDI Friend
BLACK
~{CTS}
~{RTS}
GND
GREEN
1: GND 2: IO1 3: IO3 4: IO5 5: VCC
The MFP has priority over whatever interrupting device is on the RC2014 bus, so its ~{IEI} is tied low.

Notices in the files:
BITSY.kicad_pcb:
© 2025 Rob Gowin.
Licensed under CERN-OHL-S
CONTROL.kicad_sch:
Licensed under CC-BY-SA-NC 4.0.
SRAM_SIMM_1MB/SRAM_SIMM_1MB.kicad_pcb:
Licensed under CC BY-NC-SA 4.0.
